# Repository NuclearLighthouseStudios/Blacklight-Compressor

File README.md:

# Blacklight UV LED Compressor

These are the KiCAD schematics and board layout filed for my Blacklight UV LED Compressor.  
If you just want the Gerber files or a PDF of the schematic check out the releases tab for downloads.

This PCB should be easily manufacturable with most online PCB houses by just uploading the gerber files.

This board is designed to be used with my Switchboard Pedal IO PCB which you can find [here](https://github.com/NuclearLighthouseStudios/Switchboard).

## BOM

| Reference   | Quantity | Value  | Description                                          |
| :---------- | -------: | -----: | :--------------------------------------------------- |
| C1 C4 C6    | 3        | 100n   | WIMA MKS2 63V                                        |
| C2 C5       | 2        | 1µ     | WIMA MKS2 50V                                        |
| C3          | 1        | 470n   | WIMA MKS2 50V                                        |
| C7          | 1        | 10µ    | Electrolytic capacitor, 16V                          |
| C8 C9       | 2        | 47µ    | Electrolytic capacitor, 16V                          |
| D1 D2       | 2        |        | UV LED 400nm, ~3.2V forward voltage drop             |
|             | 2        |        | 7.5mm LED standoff                                   |
| J1          | 1        |        | Pin Header, 6 pins, 2.54mm spacing                   |
| J2          | 1        |        | DC Barrel Jack with internal switch                  |
| Q1 Q2 Q3 Q4 | 4        | BC547B | 0.1A Ic, 45V Vce, Small Signal NPN Transistor, TO-92 |
| R1 R2 R5    | 3        | 1M     | Metal film resistor 1%, DIN 0207                     |
| R3 R7       | 2        | 10k    | Metal film resistor 1%, DIN 0207                     |
| R4          | 1        | 4.7k   | Metal film resistor 1%, DIN 0207                     |
| R6 R10 R13  | 3        | 100k   | Metal film resistor 1%, DIN 0207                     |
| R8          | 1        | 100    | Metal film resistor 1%, DIN 0207                     |
| R9          | 1        | 39k    | Metal film resistor 1%, DIN 0207                     |
| R11         | 1        | 47k    | Metal film resistor 1%, DIN 0207                     |
| R12         | 1        | 2.7k   | Metal film resistor 1%, DIN 0207                     |
| R14         | 1        | 82k    | Metal film resistor 1%, DIN 0207                     |
| R15 R16     | 2        | 1k     | Metal film resistor 1%, DIN 0207                     |
| RV1 RV2     | 2        | 100k   | Alps RK09K1130C94 Potentiometer                      |

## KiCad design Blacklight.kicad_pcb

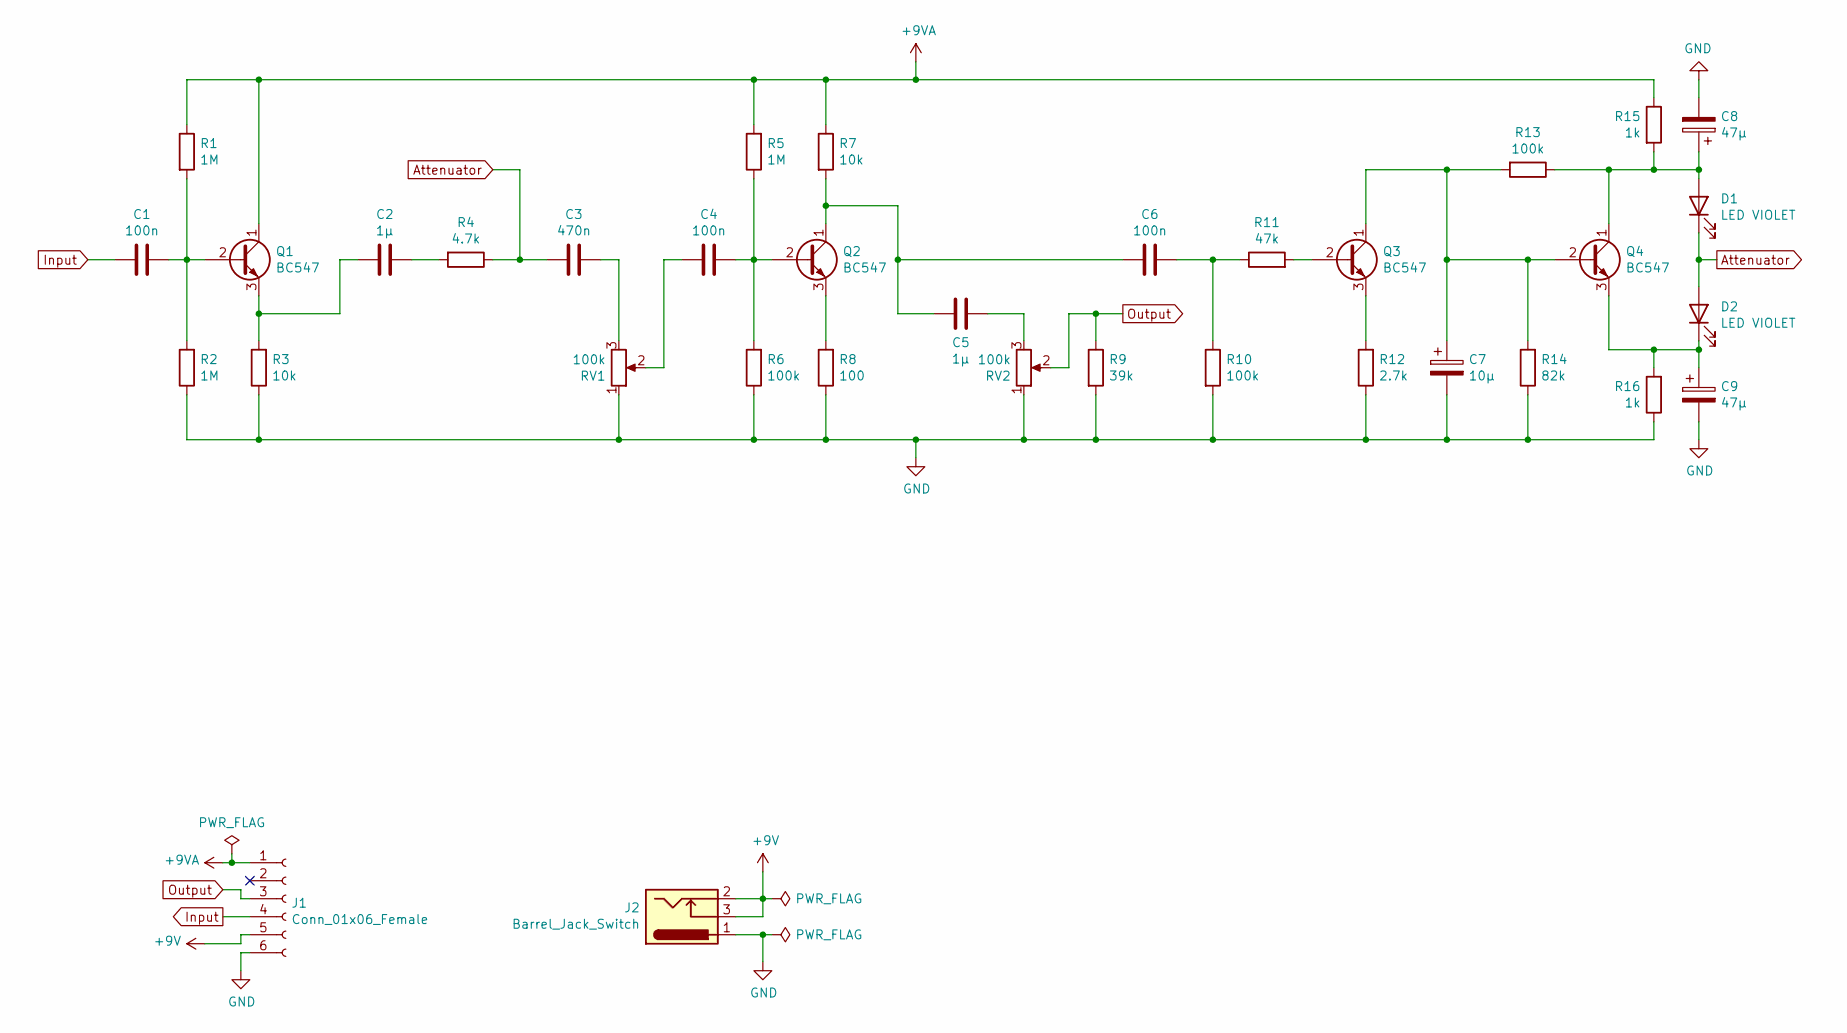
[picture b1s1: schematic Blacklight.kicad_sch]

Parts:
C1, C4, C6: 100n; C_Rect_L7.2mm_W2.5mm_P5.00mm_FKS2_FKP2_MKS2_MKP2
C2, C5: 1µ; C_Rect_L7.2mm_W4.5mm_P5.00mm_FKS2_FKP2_MKS2_MKP2
C3: 470n; C_Rect_L7.2mm_W3.5mm_P5.00mm_FKS2_FKP2_MKS2_MKP2
C7: 10µ; CP_Radial_D5.0mm_P2.50mm
C8, C9: 47µ; CP_Radial_D5.0mm_P2.50mm
D1, D2: LED VIOLET; LED_D5.0mm
J1: Conn_01x06_Female; PinHeader_1x06_P2.54mm_Vertical
J2: Barrel_Jack_Switch; BarrelJack_Horizontal_Short
Q1, Q2, Q3, Q4: BC547; TO-92_Wide
R1, R2, R5: 1M; R_Axial_DIN0207_L6.3mm_D2.5mm_P2.54mm_Vertical
R3, R7: 10k; R_Axial_DIN0207_L6.3mm_D2.5mm_P2.54mm_Vertical
R4: 4.7k; R_Axial_DIN0207_L6.3mm_D2.5mm_P2.54mm_Vertical
R6, R10: 100k; R_Axial_DIN0207_L6.3mm_D2.5mm_P2.54mm_Vertical
R8: 100; R_Axial_DIN0207_L6.3mm_D2.5mm_P2.54mm_Vertical
R9: 39k; R_Axial_DIN0207_L6.3mm_D2.5mm_P7.62mm_Horizontal
R11: 47k; R_Axial_DIN0207_L6.3mm_D2.5mm_P2.54mm_Vertical
R12: 2.7k; R_Axial_DIN0207_L6.3mm_D2.5mm_P2.54mm_Vertical
R13: 100k; R_Axial_DIN0207_L6.3mm_D2.5mm_P7.62mm_Horizontal
R14: 82k; R_Axial_DIN0207_L6.3mm_D2.5mm_P2.54mm_Vertical
R15, R16: 1k; R_Axial_DIN0207_L6.3mm_D2.5mm_P2.54mm_Vertical
RV1, RV2: 100k; Potentiometer_Alps_RK09K_Single_Vertical

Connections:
+9V: J1.5, J2.2, J2.3
+9VA: J1.1, Q1.1 (C), R1.1, R5.2, R7.1, R15.1
Attenuator: C3.2, D1.1 (K), D2.2 (A), R4.1
GND: C7.2, C8.2, C9.2, J1.6, J2.1, R2.1, R3.1, R6.1, R8.1, R9.2, R10.2, R12.1, R14.1, R16.1, RV1.1, RV2.1
Input: C1.2, J1.4
unnamed: C1.1, Q1.2 (B), R1.2, R2.2
unnamed: C2.1, R4.2
unnamed: C2.2, Q1.3 (E), R3.2
unnamed: C3.1, RV1.3
unnamed: C4.1, Q2.2 (B), R5.1, R6.2
unnamed: C4.2, RV1.2
unnamed: C5.1, RV2.3
unnamed: C5.2, C6.2, Q2.1 (C), R7.2
unnamed: C6.1, R10.1, R11.1
unnamed: C7.1, Q3.1 (C), Q4.2 (B), R13.2, R14.2
unnamed: C8.1, D1.2 (A), Q4.1 (C), R13.1, R15.2
unnamed: C9.1, D2.1 (K), Q4.3 (E), R16.2
unnamed: Q2.3 (E), R8.2
unnamed: Q3.2 (B), R11.2
unnamed: Q3.3 (E), R12.2
Output: J1.3, R9.1, RV2.2

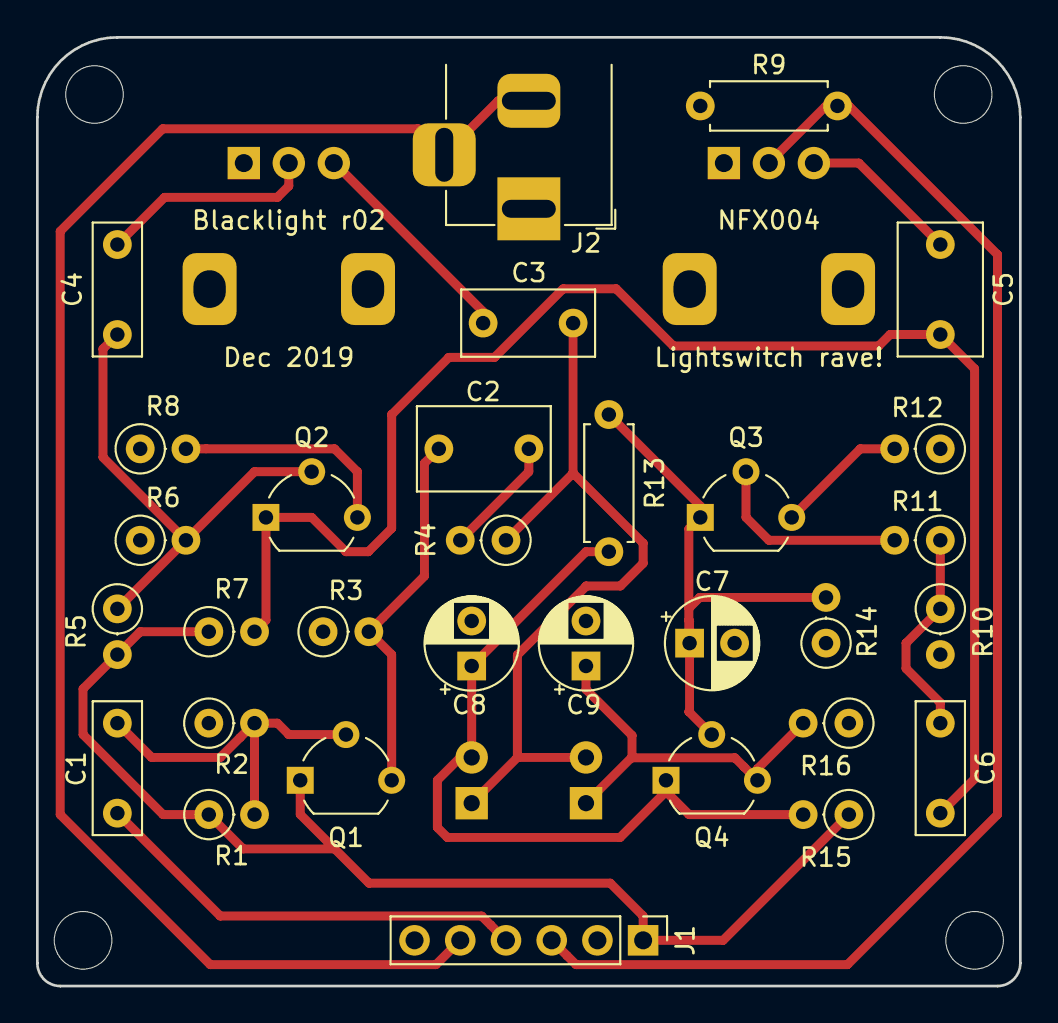
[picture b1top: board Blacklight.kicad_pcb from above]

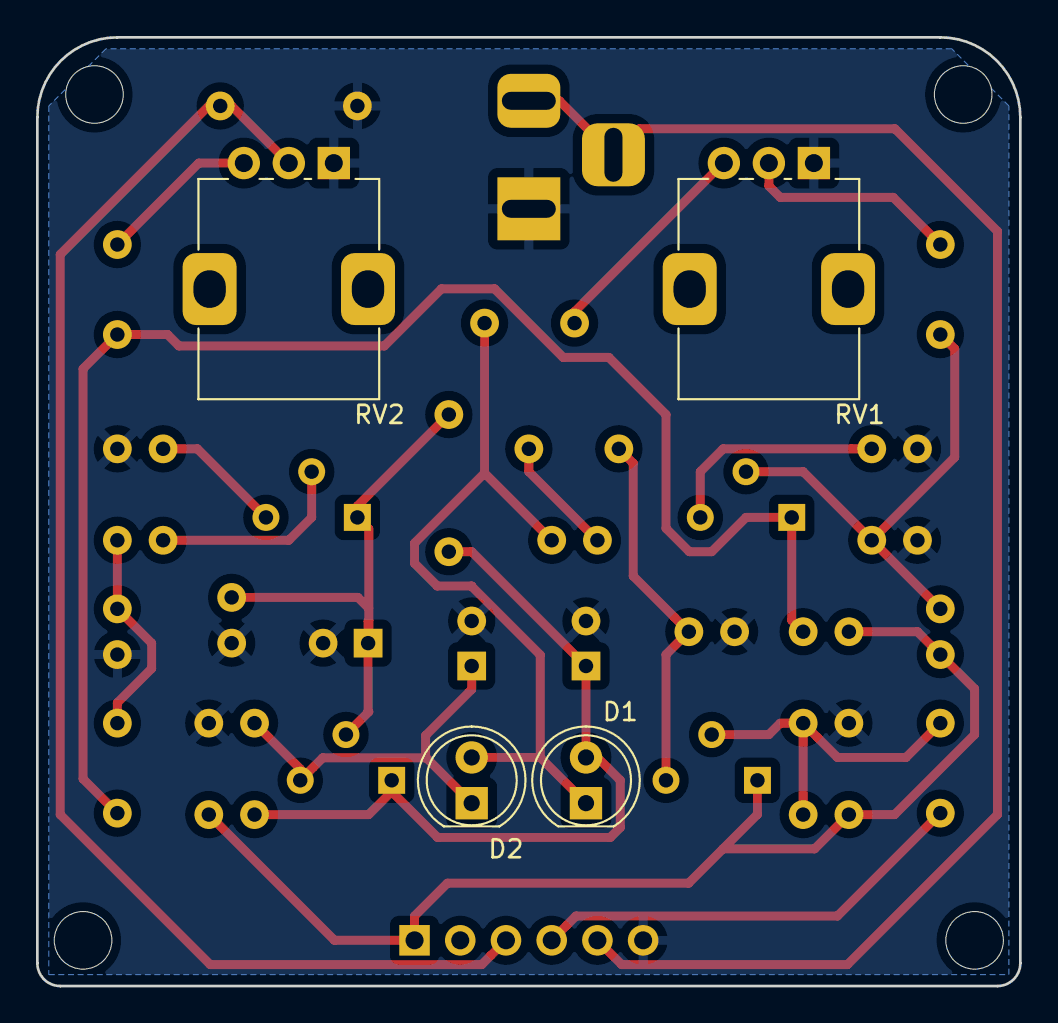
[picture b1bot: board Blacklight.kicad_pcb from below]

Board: 2 copper layers, 54.6 x 52.7 mm, 35 parts (4 on the bottom side), 21 nets.

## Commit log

2020-11-16 Initial commit! Yay!
2020-11-16 Improve BOM a little
2020-11-16 Add more B
2020-12-30 Fix mistake in BOM
2020-12-31 Update cap voltages
2021-03-26 Include LED standoffs in BOM
2022-08-14 Migrate to KiCAD 6
2022-08-14 Update symbols/footprints
2022-08-14 Fix DRC errors

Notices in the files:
Blacklight.kicad_sch:
CC BY-NC-SA
